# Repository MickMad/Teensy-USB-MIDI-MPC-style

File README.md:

# Teensy-USB-MIDI-MPC-style
DIY USB MIDI controller MPC style - An MPC style MIDI controller featuring a 4x4 FSR matrix and based on Teensy 3.0, fully compatible with the Teensy Audio Adaptor Board

More info here:

https://hackaday.io/project/1601-diy-usb-midi-controller-mpc-style

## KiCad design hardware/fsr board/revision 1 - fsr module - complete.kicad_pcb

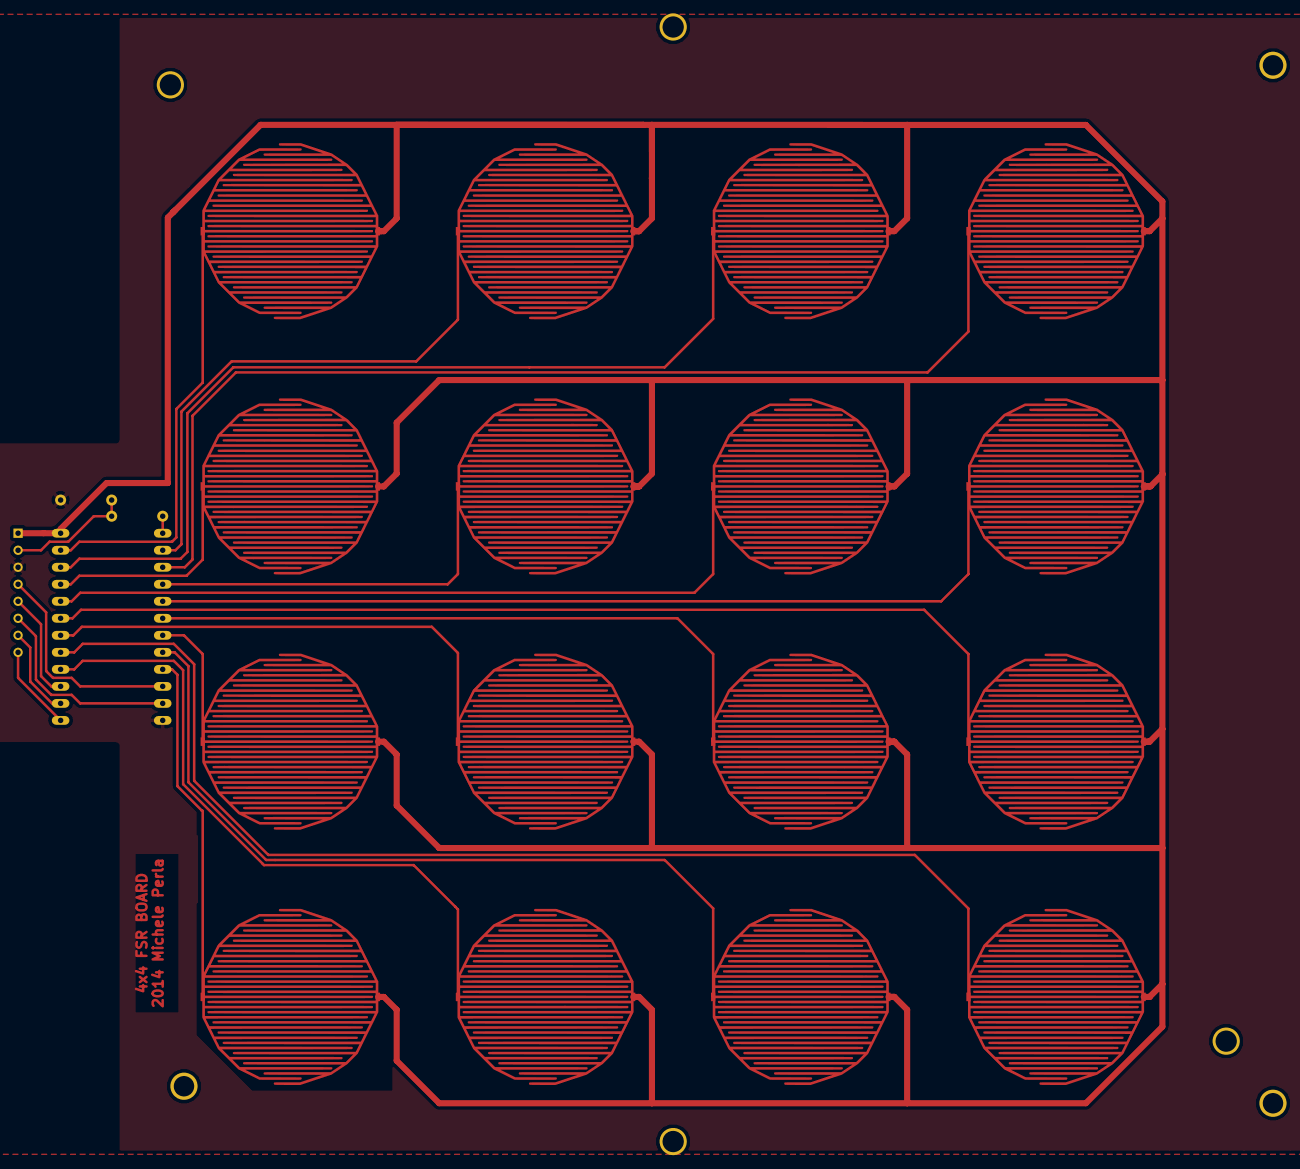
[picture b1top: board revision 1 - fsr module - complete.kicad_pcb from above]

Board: 2 copper layers, 27 parts (0 on the bottom side), 25 nets.

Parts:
1PIN, 1PIN#2, 1PIN#3, 1PIN#4, 1PIN#5, 1PIN#6, 1PIN#7: P***; 1pin
IC1: 4067D; 40xx-DIL24-6
P1: CONN_8; SIL-8
R1, R2, R3, R4, R5, R6, R7, R8, R9, R10, R11, R12, R13, R14, R15, R16: FSR; FSR-15-mil
R17: 4K7; R3-LARGE_PADS
R18: 10K; R3-LARGE_PADS

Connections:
+5V: IC1.24, P1.1, R1.1, R2.1, R3.1, R4.1, R5.1, R6.1, R7.1, R8.1, R9.1, R10.1, R11.1, R12.1, R13.1, R14.1, R15.1, R16.1
A: IC1.10, P1.4
B: IC1.11, P1.6
C: IC1.14, P1.7
D: IC1.13, P1.8
GND: IC1.12, P1.3, R18.2
INH1: IC1.15, P1.5
unnamed: IC1.19, R14.2
unnamed: IC1.18, R6.2
unnamed: IC1.17, R13.2
unnamed: IC1.1, R17.1
unnamed: IC1.21, R3.2
unnamed: IC1.16, R5.2
unnamed: IC1.6, R10.2
unnamed: IC1.22, R12.2
unnamed: IC1.2, R8.2
unnamed: IC1.23, R4.2
unnamed: IC1.5, R15.2
unnamed: IC1.20, R11.2
unnamed: IC1.4, R7.2
unnamed: IC1.7, R2.2
unnamed: IC1.8, R9.2
unnamed: IC1.9, R1.2
unnamed: IC1.3, R16.2
OUT1: P1.2, R17.2, R18.1

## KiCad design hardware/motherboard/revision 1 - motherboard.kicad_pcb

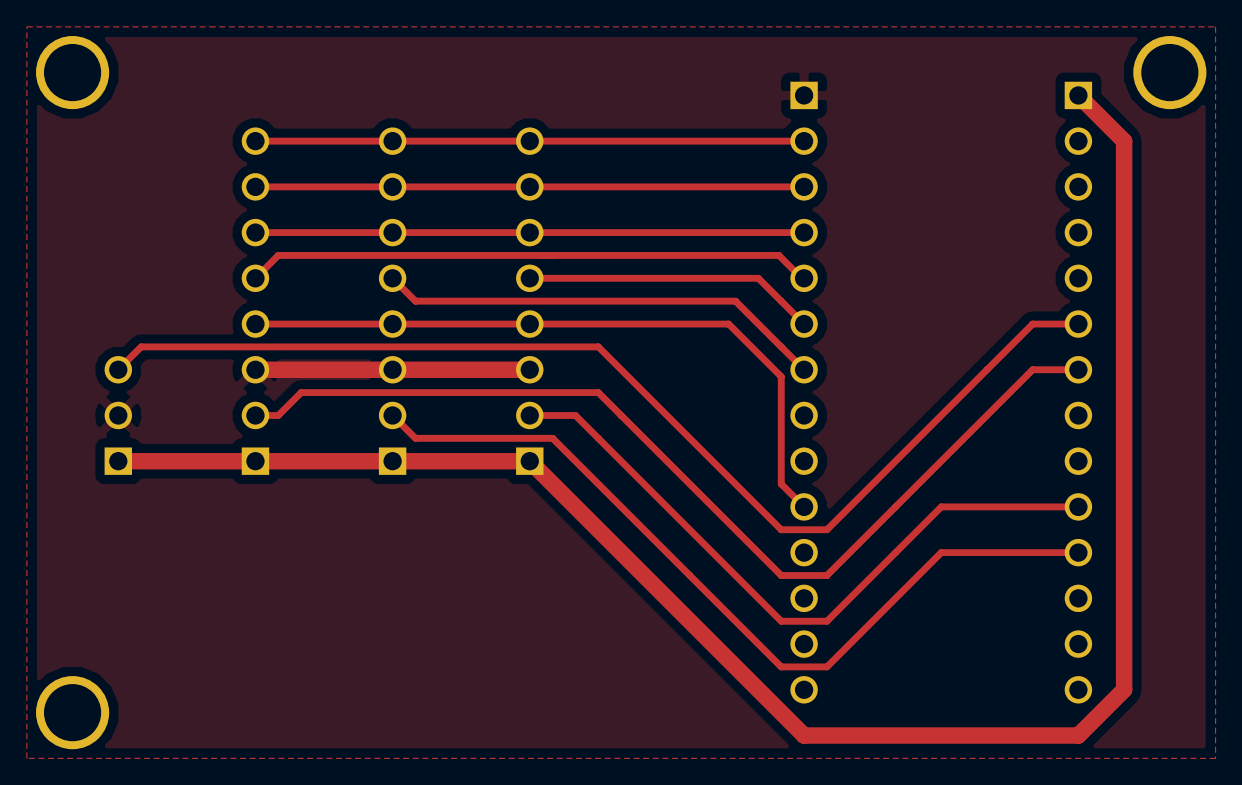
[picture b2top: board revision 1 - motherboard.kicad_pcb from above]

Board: 2 copper layers, 9 parts (0 on the bottom side), 13 nets.

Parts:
1PIN, 1PIN#2, 1PIN#3: P***; 1pin
J1, J2: SIL14; SIL-14
P1, P2, P3: CONN_8; SIL-8
P4: CONN_3; SIL-3

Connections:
+5V: J2.1, P1.1, P2.1, P3.1, P4.1
A: J1.10, P1.4, P2.4, P3.4
B: J1.4, P1.6, P2.6, P3.6
C: J1.3, P1.7, P2.7, P3.7
D: J1.2, P1.8, P2.8, P3.8
GND: J1.1, P1.3, P2.3, P3.3, P4.2
INH1: J1.5, P1.5
INH2: J1.7, P2.5
INH3: J1.6, P3.5
OUT1: J2.7, P1.2
OUT2: J2.11, P2.2
OUT3: J2.10, P3.2
OUT4: J2.6, P4.3

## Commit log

2015-02-27 mass update of Git repos
2015-02-27 Update README.md
    Added link to Hackaday.io page
